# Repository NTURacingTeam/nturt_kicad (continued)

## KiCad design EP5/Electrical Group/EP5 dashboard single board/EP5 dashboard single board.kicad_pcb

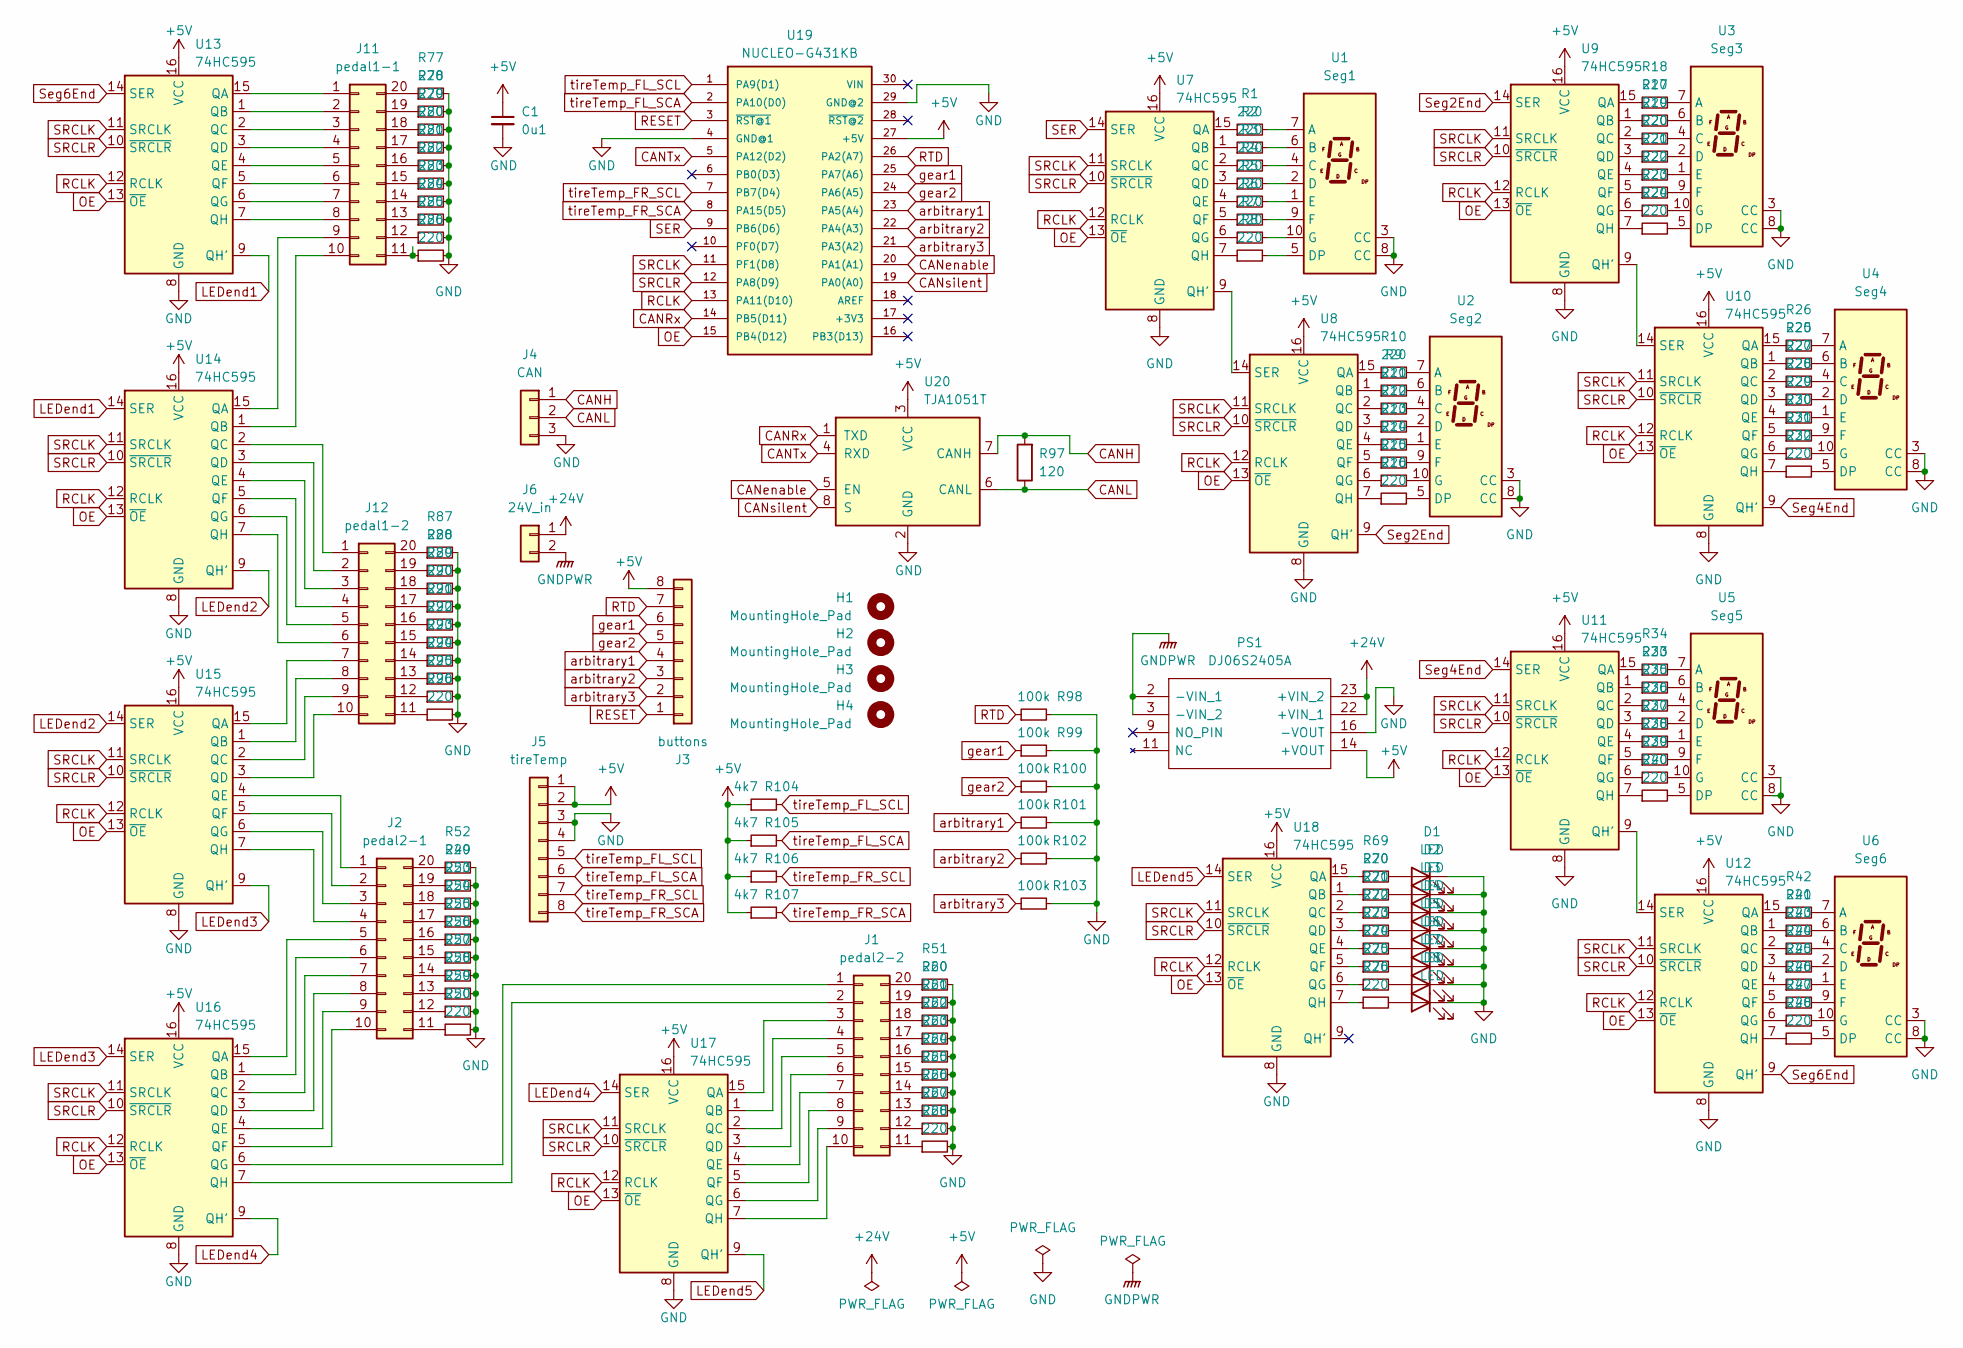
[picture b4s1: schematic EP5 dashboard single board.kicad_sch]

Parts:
C1: 0u1; C_0805_2012Metric_Pad1.18x1.45mm_HandSolder
D1, D2, D3, D4, D5, D6, D7, D8: LED; LED_PLCC_2835
H1, H2, H3, H4: MountingHole_Pad; MountingHole_2.2mm_M2_DIN965_Pad_TopBottom
J1: pedal2-2; DIP-20_W7.62mm
J2: pedal2-1; DIP-20_W7.62mm
J3: buttons; JST_XH_B8B-XH-A_1x08_P2.50mm_Vertical
J4: CAN; JST_XH_B3B-XH-A_1x03_P2.50mm_Vertical
J5: tireTemp; JST_XH_B8B-XH-A_1x08_P2.50mm_Vertical
J6: 24V_in; JST_XH_B2B-XH-A_1x02_P2.50mm_Vertical
J11: pedal1-1; DIP-20_W7.62mm
J12: pedal1-2; DIP-20_W7.62mm
PS1: DJ06S2405A; DJ06S4805A; Mouser Part Number 108-DJ06S4805A
R1, R2, R3, R4, R5, R6, R7, R8, R9, R10, R11, R12, R13, R14, R15, R16, R17, R18, R19, R20, R21, R22, R23, R24, R25, R26, R27, R28, R29, R30, R31, R32, R33, R34, R35, R36, R37, R38, R39, R40, R41, R42, R43, R44, R45, R46, R47, R48, R49, R50, R51, R52, R53, R54, R55, R56, R57, R58, R59, R60, R61, R62, R63, R64, R65, R66, R67, R68, R69, R70, R71, R72, R73, R74, R75, R76, R77, R78, R79, R80, R81, R82, R83, R84, R85, R86, R87, R88, R89, R90, R91, R92, R93, R94, R95, R96: 220; R_0603_1608Metric_Pad0.98x0.95mm_HandSolder
R97: 120; R_0805_2012Metric
R98, R99, R100, R101, R102, R103: 100k; R_0805_2012Metric
R104, R105, R106, R107: 4k7; R_0805_2012Metric
U1: Seg1; 7SegmentLED_LTS6760_LTS6780
U2: Seg2; 7SegmentLED_LTS6760_LTS6780
U3: Seg3; 7SegmentLED_LTS6760_LTS6780
U4: Seg4; 7SegmentLED_LTS6760_LTS6780
U5: Seg5; 7SegmentLED_LTS6760_LTS6780
U6: Seg6; 7SegmentLED_LTS6760_LTS6780
U7, U8, U9, U10, U11, U12, U13, U14, U15, U16, U17, U18: 74HC595; SOIC-16_3.9x9.9mm_P1.27mm
U19: NUCLEO-G431KB; MANUFACTURER_PART_NUMBER NUCLEO-F303K8
U20: TJA1051T; SOIC-8_3.9x4.9mm_P1.27mm

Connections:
+5V: C1.1, J3.8, J5.1, J5.2, PS1.14 (+VOUT), R104.1, R105.1, R106.1, R107.1, U7.16 (VCC), U8.16 (VCC), U9.16 (VCC), U10.16 (VCC), U11.16 (VCC), U12.16 (VCC), U13.16 (VCC), U14.16 (VCC), U15.16 (VCC), U16.16 (VCC), U17.16 (VCC), U18.16 (VCC), U19.27 (+5V), U20.3 (VCC)
+24V: J6.1, PS1.22 (+VIN_1), PS1.23 (+VIN_2)
CANH: J4.1, R97.2, U20.7 (CANH)
CANL: J4.2, R97.1, U20.6 (CANL)
CANRx: U19.14 (PB5(D11)), U20.1 (TXD)
CANTx: U19.5 (PA12(D2)), U20.4 (RXD)
CANenable: U19.20 (PA1(A1)), U20.5 (EN)
CANsilent: U19.19 (PA0(A0)), U20.8 (S)
GND: C1.2, D1.1 (K), D2.1 (K), D3.1 (K), D4.1 (K), D5.1 (K), D6.1 (K), D7.1 (K), D8.1 (K), J4.3, J5.3, J5.4, PS1.16 (-VOUT), R49.2, R50.2, R51.2, R52.2, R53.2, R54.2, R55.2, R56.2, R57.2, R58.2, R59.2, R60.2, R61.2, R62.2, R63.2, R64.2, R65.2, R66.2, R67.2, R68.2, R77.2, R78.2, R79.2, R80.2, R81.2, R82.2, R83.2, R84.2, R85.2, R86.2, R87.2, R88.2, R89.2, R90.2, R91.2, R92.2, R93.2, R94.2, R95.2, R96.2, R98.2, R99.2, R100.2, R101.2, R102.2, R103.2, U1.3 (CC), U1.8 (CC), U2.3 (CC), U2.8 (CC), U3.3 (CC), U3.8 (CC), U4.3 (CC), U4.8 (CC), U5.3 (CC), U5.8 (CC), U6.3 (CC), U6.8 (CC), U7.8 (GND), U8.8 (GND), U9.8 (GND), U10.8 (GND), U11.8 (GND), U12.8 (GND), U13.8 (GND), U14.8 (GND), U15.8 (GND), U16.8 (GND), U17.8 (GND), U18.8 (GND), U19.4 (GND@1), U19.29 (GND@2), U20.2 (GND)
GNDPWR: J6.2, PS1.2 (-VIN_1), PS1.3 (-VIN_2)
LEDend1: U13.9 (QH'), U14.14 (SER)
LEDend2: U14.9 (QH'), U15.14 (SER)
LEDend3: U15.9 (QH'), U16.14 (SER)
LEDend4: U16.9 (QH'), U17.14 (SER)
LEDend5: U17.9 (QH'), U18.14 (SER)
unnamed: D1.2 (A), R69.2
unnamed: D2.2 (A), R70.2
unnamed: D3.2 (A), R71.2
unnamed: D4.2 (A), R72.2
unnamed: D5.2 (A), R73.2
unnamed: D6.2 (A), R74.2
unnamed: D7.2 (A), R75.2
unnamed: D8.2 (A), R76.2
unnamed: J1.1, U16.6 (QG)
unnamed: J1.2, U16.7 (QH)
unnamed: J1.3, U17.15 (QA)
unnamed: J1.4, U17.1 (QB)
unnamed: J1.5, U17.2 (QC)
unnamed: J1.6, U17.3 (QD)
unnamed: J1.7, U17.4 (QE)
unnamed: J1.8, U17.5 (QF)
unnamed: J1.9, U17.6 (QG)
unnamed: J1.10, U17.7 (QH)
unnamed: J1.11, R68.1
unnamed: J1.12, R67.1
unnamed: J1.13, R66.1
unnamed: J1.14, R65.1
unnamed: J1.15, R64.1
unnamed: J1.16, R63.1
unnamed: J1.17, R62.1
unnamed: J1.18, R61.1
unnamed: J1.19, R60.1
unnamed: J1.20, R51.1
unnamed: J2.1, U15.4 (QE)
unnamed: J2.2, U15.5 (QF)
unnamed: J2.3, U15.6 (QG)
unnamed: J2.4, U15.7 (QH)
unnamed: J2.5, U16.15 (QA)
unnamed: J2.6, U16.1 (QB)
unnamed: J2.7, U16.2 (QC)
unnamed: J2.8, U16.3 (QD)
unnamed: J2.9, U16.4 (QE)
unnamed: J2.10, U16.5 (QF)
unnamed: J2.11, R50.1
unnamed: J2.12, R59.1
unnamed: J2.13, R58.1
unnamed: J2.14, R57.1
unnamed: J2.15, R56.1
unnamed: J2.16, R55.1
unnamed: J2.17, R54.1
unnamed: J2.18, R53.1
unnamed: J2.19, R49.1
unnamed: J2.20, R52.1
unnamed: J11.1, U13.15 (QA)
unnamed: J11.2, U13.1 (QB)
unnamed: J11.3, U13.2 (QC)
unnamed: J11.4, U13.3 (QD)
unnamed: J11.5, U13.4 (QE)
unnamed: J11.6, U13.5 (QF)
unnamed: J11.7, U13.6 (QG)
unnamed: J11.8, U13.7 (QH)
unnamed: J11.9, U14.15 (QA)
unnamed: J11.10, U14.1 (QB)
unnamed: J11.11, R86.1
unnamed: J11.12, R85.1
unnamed: J11.13, R84.1
unnamed: J11.14, R83.1
unnamed: J11.15, R82.1
unnamed: J11.16, R81.1
unnamed: J11.17, R80.1
unnamed: J11.18, R79.1
unnamed: J11.19, R78.1
unnamed: J11.20, R77.1
unnamed: J12.1, U14.2 (QC)
unnamed: J12.2, U14.3 (QD)
unnamed: J12.3, U14.4 (QE)
unnamed: J12.4, U14.5 (QF)
unnamed: J12.5, U14.6 (QG)
unnamed: J12.6, U14.7 (QH)
unnamed: J12.7, U15.15 (QA)
unnamed: J12.8, U15.1 (QB)
unnamed: J12.9, U15.2 (QC)
unnamed: J12.10, U15.3 (QD)
unnamed: J12.11, R96.1
unnamed: J12.12, R95.1
unnamed: J12.13, R94.1
unnamed: J12.14, R93.1
unnamed: J12.15, R92.1
unnamed: J12.16, R91.1
unnamed: J12.17, R90.1
unnamed: J12.18, R89.1
unnamed: J12.19, R88.1
unnamed: J12.20, R87.1
unnamed: R1.2, U1.7 (A)
unnamed: R2.2, U1.6 (B)
unnamed: R3.2, U1.4 (C)
unnamed: R4.2, U1.2 (D)
unnamed: R8.2, U1.5 (DP)
unnamed: R5.2, U1.1 (E)
unnamed: R6.2, U1.9 (F)
unnamed: R7.2, U1.10 (G)
unnamed: R10.2, U2.7 (A)
unnamed: R9.2, U2.6 (B)
unnamed: R11.2, U2.4 (C)
unnamed: R12.2, U2.2 (D)
unnamed: R16.2, U2.5 (DP)
unnamed: R13.2, U2.1 (E)
unnamed: R14.2, U2.9 (F)
unnamed: R15.2, U2.10 (G)
unnamed: R18.2, U3.7 (A)
unnamed: R17.2, U3.6 (B)
unnamed: R19.2, U3.4 (C)
unnamed: R20.2, U3.2 (D)
unnamed: R24.2, U3.5 (DP)
unnamed: R21.2, U3.1 (E)
unnamed: R22.2, U3.9 (F)
unnamed: R23.2, U3.10 (G)
unnamed: R26.2, U4.7 (A)
unnamed: R25.2, U4.6 (B)
unnamed: R27.2, U4.4 (C)
unnamed: R28.2, U4.2 (D)
unnamed: R32.2, U4.5 (DP)
unnamed: R29.2, U4.1 (E)
unnamed: R30.2, U4.9 (F)
unnamed: R31.2, U4.10 (G)
unnamed: R34.2, U5.7 (A)
unnamed: R33.2, U5.6 (B)
unnamed: R35.2, U5.4 (C)
unnamed: R36.2, U5.2 (D)
unnamed: R40.2, U5.5 (DP)
unnamed: R37.2, U5.1 (E)
unnamed: R38.2, U5.9 (F)
unnamed: R39.2, U5.10 (G)
unnamed: R42.2, U6.7 (A)
unnamed: R41.2, U6.6 (B)
unnamed: R43.2, U6.4 (C)
unnamed: R44.2, U6.2 (D)
unnamed: R48.2, U6.5 (DP)
unnamed: R45.2, U6.1 (E)
unnamed: R46.2, U6.9 (F)
unnamed: R47.2, U6.10 (G)
unnamed: R1.1, U7.15 (QA)
unnamed: R2.1, U7.1 (QB)
unnamed: R3.1, U7.2 (QC)
unnamed: R4.1, U7.3 (QD)
unnamed: R5.1, U7.4 (QE)
unnamed: R6.1, U7.5 (QF)
unnamed: R7.1, U7.6 (QG)
unnamed: U7.9 (QH'), U8.14 (SER)
unnamed: R8.1, U7.7 (QH)
unnamed: R10.1, U8.15 (QA)
unnamed: R9.1, U8.1 (QB)
unnamed: R11.1, U8.2 (QC)
unnamed: R12.1, U8.3 (QD)
unnamed: R13.1, U8.4 (QE)
unnamed: R14.1, U8.5 (QF)
unnamed: R15.1, U8.6 (QG)
unnamed: R16.1, U8.7 (QH)
unnamed: R18.1, U9.15 (QA)
unnamed: R17.1, U9.1 (QB)
unnamed: R19.1, U9.2 (QC)
unnamed: R20.1, U9.3 (QD)
unnamed: R21.1, U9.4 (QE)
unnamed: R22.1, U9.5 (QF)
unnamed: R23.1, U9.6 (QG)
unnamed: R24.1, U9.7 (QH)
unnamed: R26.1, U10.15 (QA)
unnamed: R25.1, U10.1 (QB)
unnamed: R27.1, U10.2 (QC)
unnamed: R28.1, U10.3 (QD)
unnamed: R29.1, U10.4 (QE)
unnamed: R30.1, U10.5 (QF)
unnamed: R31.1, U10.6 (QG)
unnamed: R32.1, U10.7 (QH)
unnamed: U9.9 (QH'), U10.14 (SER)
unnamed: R34.1, U11.15 (QA)
unnamed: R33.1, U11.1 (QB)
unnamed: R35.1, U11.2 (QC)
unnamed: R36.1, U11.3 (QD)
unnamed: R37.1, U11.4 (QE)
unnamed: R38.1, U11.5 (QF)
unnamed: R39.1, U11.6 (QG)
unnamed: U11.9 (QH'), U12.14 (SER)
unnamed: R40.1, U11.7 (QH)
unnamed: R42.1, U12.15 (QA)
unnamed: R41.1, U12.1 (QB)
unnamed: R43.1, U12.2 (QC)
unnamed: R44.1, U12.3 (QD)
unnamed: R45.1, U12.4 (QE)
unnamed: R46.1, U12.5 (QF)
unnamed: R47.1, U12.6 (QG)
unnamed: R48.1, U12.7 (QH)
unnamed: R69.1, U18.15 (QA)
unnamed: R70.1, U18.1 (QB)
unnamed: R71.1, U18.2 (QC)
unnamed: R72.1, U18.3 (QD)
unnamed: R73.1, U18.4 (QE)
unnamed: R74.1, U18.5 (QF)
unnamed: R75.1, U18.6 (QG)
unnamed: R76.1, U18.7 (QH)
OE: U7.13 (~OE), U8.13 (~OE), U9.13 (~OE), U10.13 (~OE), U11.13 (~OE), U12.13 (~OE), U13.13 (~OE), U14.13 (~OE), U15.13 (~OE), U16.13 (~OE), U17.13 (~OE), U18.13 (~OE), U19.15 (PB4(D12))
RCLK: U7.12 (RCLK), U8.12 (RCLK), U9.12 (RCLK), U10.12 (RCLK), U11.12 (RCLK), U12.12 (RCLK), U13.12 (RCLK), U14.12 (RCLK), U15.12 (RCLK), U16.12 (RCLK), U17.12 (RCLK), U18.12 (RCLK), U19.13 (PA11(D10))
RESET: J3.1, U19.3 (~RST@1)
RTD: J3.7, R98.1, U19.26 (PA2(A7))
SER: U7.14 (SER), U19.9 (PB6(D6))
SRCLK: U7.11 (SRCLK), U8.11 (SRCLK), U9.11 (SRCLK), U10.11 (SRCLK), U11.11 (SRCLK), U12.11 (SRCLK), U13.11 (SRCLK), U14.11 (SRCLK), U15.11 (SRCLK), U16.11 (SRCLK), U17.11 (SRCLK), U18.11 (SRCLK), U19.11 (PF1(D8))
SRCLR: U7.10 (~SRCLR), U8.10 (~SRCLR), U9.10 (~SRCLR), U10.10 (~SRCLR), U11.10 (~SRCLR), U12.10 (~SRCLR), U13.10 (~SRCLR), U14.10 (~SRCLR), U15.10 (~SRCLR), U16.10 (~SRCLR), U17.10 (~SRCLR), U18.10 (~SRCLR), U19.12 (PA8(D9))
Seg2End: U8.9 (QH'), U9.14 (SER)
Seg4End: U10.9 (QH'), U11.14 (SER)
Seg6End: U12.9 (QH'), U13.14 (SER)
arbitrary1: J3.4, R101.1, U19.23 (PA5(A4))
arbitrary2: J3.3, R102.1, U19.22 (PA4(A3))
arbitrary3: J3.2, R103.1, U19.21 (PA3(A2))
gear1: J3.6, R99.1, U19.25 (PA7(A6))
gear2: J3.5, R100.1, U19.24 (PA6(A5))
tireTemp_FL_SCA: J5.6, R105.2, U19.2 (PA10(D0))
tireTemp_FL_SCL: J5.5, R104.2, U19.1 (PA9(D1))
tireTemp_FR_SCA: J5.8, R107.2, U19.8 (PA15(D5))
tireTemp_FR_SCL: J5.7, R106.2, U19.7 (PB7(D4))

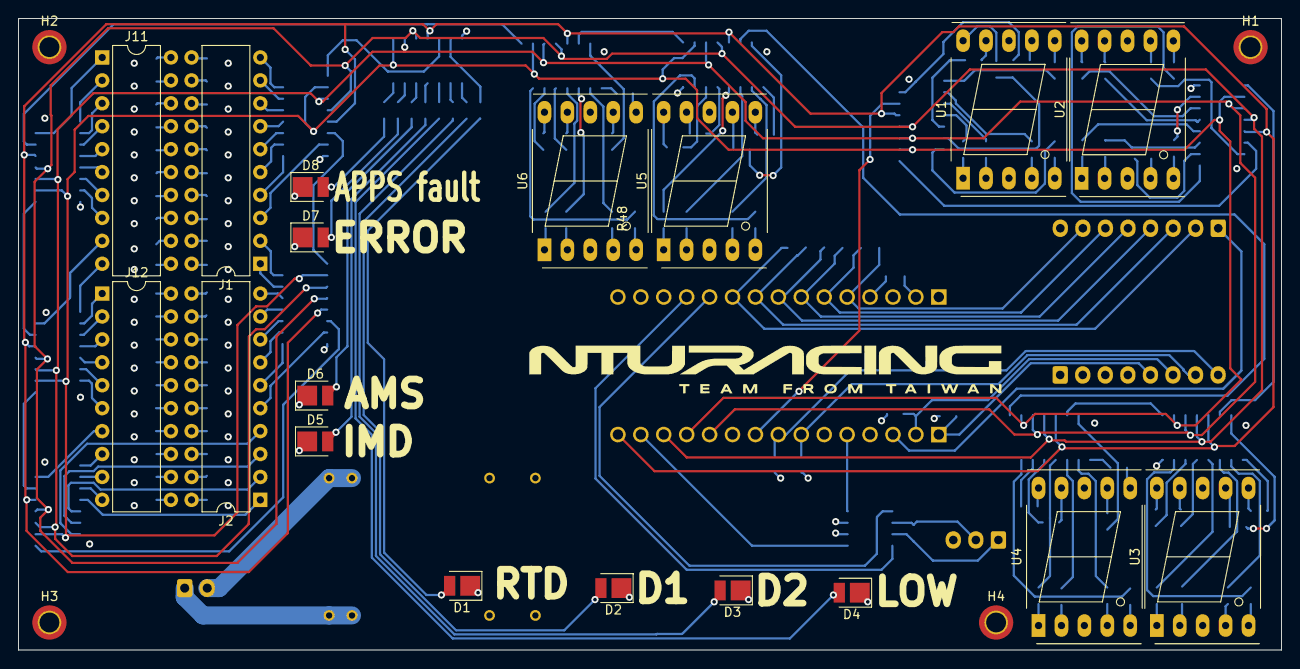
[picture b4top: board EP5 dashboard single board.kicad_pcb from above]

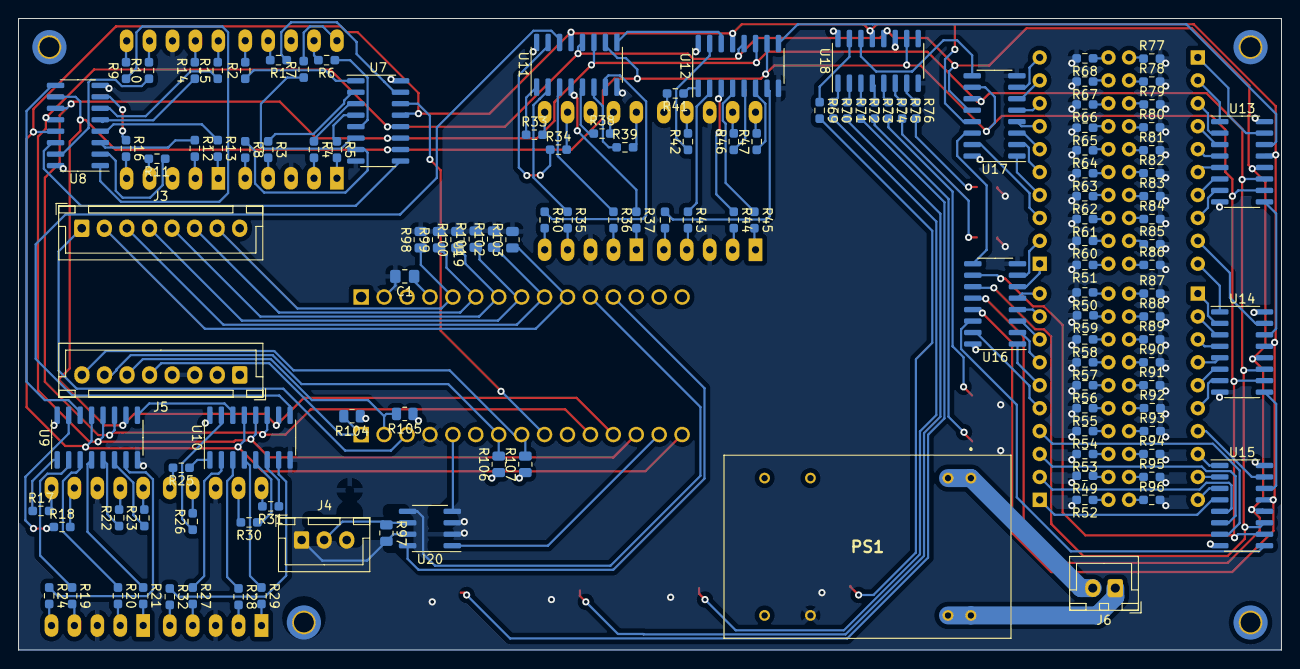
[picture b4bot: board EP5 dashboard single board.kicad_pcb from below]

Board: 4 copper layers, 140.0 x 70.0 mm, 149 parts (127 on the bottom side), 229 nets.

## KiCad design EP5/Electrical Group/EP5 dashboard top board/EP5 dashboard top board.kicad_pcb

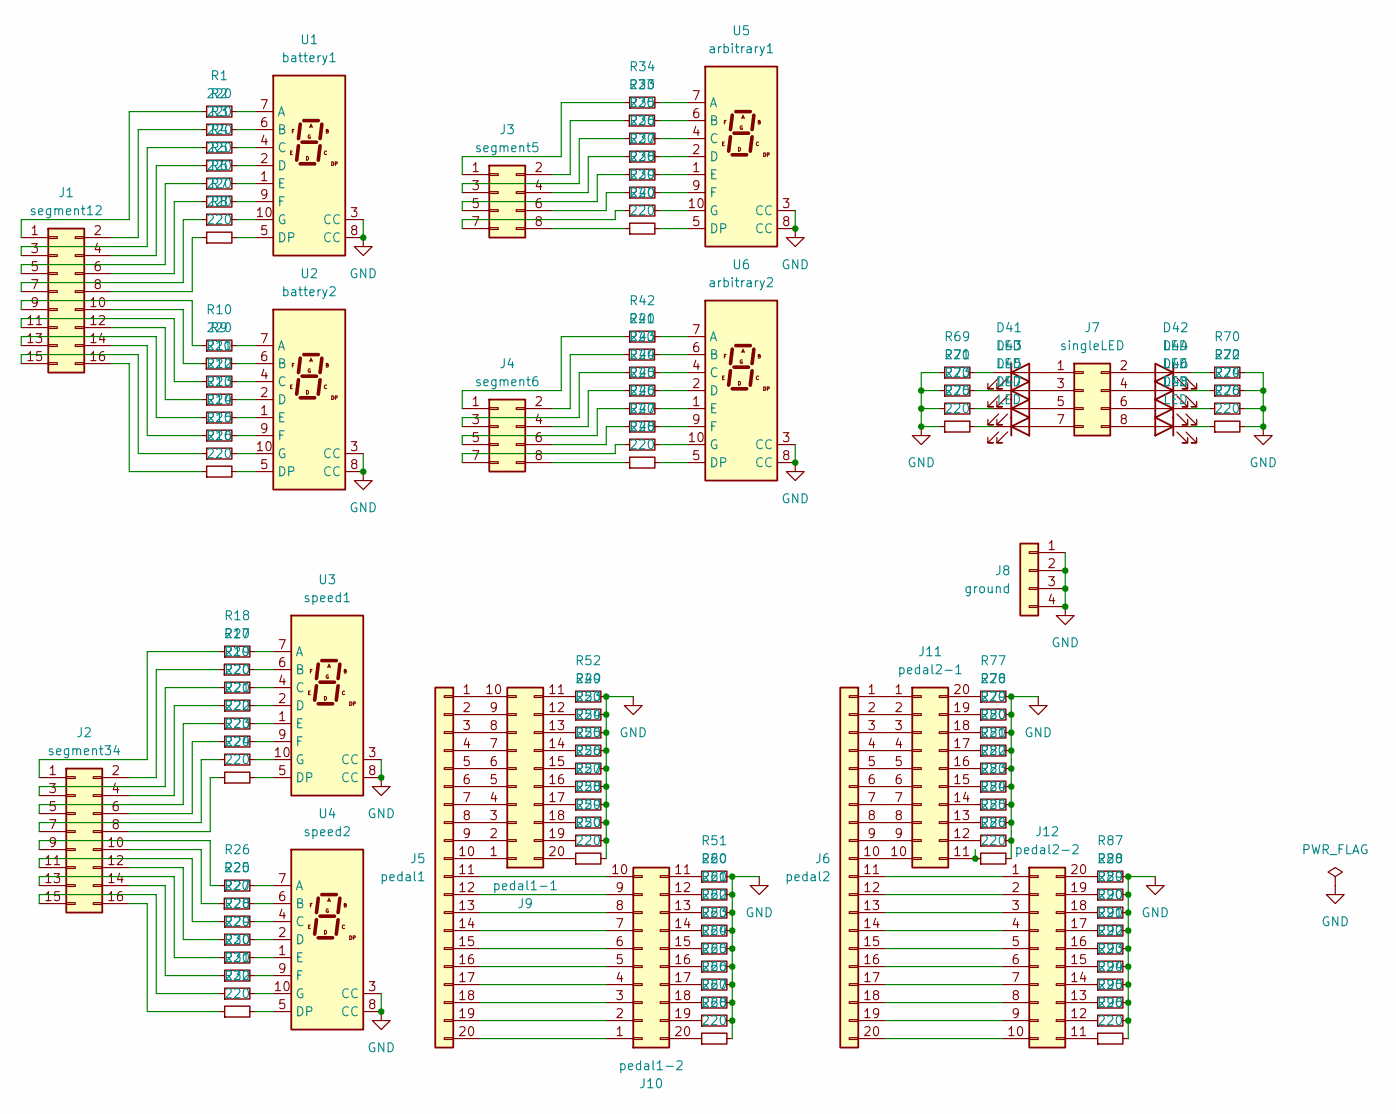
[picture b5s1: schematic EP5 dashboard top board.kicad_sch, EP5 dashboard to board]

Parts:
D41, D42, D43, D44, D45, D46, D47, D48: LED; LED_PLCC_2835
J1: segment12; PinHeader_2x08_P2.54mm_Vertical
J2: segment34; PinHeader_2x08_P2.54mm_Vertical
J3: segment5; PinHeader_2x04_P2.54mm_Vertical
J4: segment6; PinHeader_2x04_P2.54mm_Vertical
J5: pedal1; PinHeader_1x20_P2.54mm_Vertical
J6: pedal2; PinHeader_1x20_P2.54mm_Vertical
J7: singleLED; PinHeader_2x04_P2.54mm_Vertical
J8: ground; PinHeader_1x04_P2.54mm_Vertical
J9: pedal1-1; DIP-20_W7.62mm
J10: pedal1-2; DIP-20_W7.62mm
J11: pedal2-1; DIP-20_W7.62mm
J12: pedal2-2; DIP-20_W7.62mm
R1, R2, R3, R4, R5, R6, R7, R8, R9, R10, R11, R12, R13, R14, R15, R16, R17, R18, R19, R20, R21, R22, R23, R24, R25, R26, R27, R28, R29, R30, R31, R32, R33, R34, R35, R36, R37, R38, R39, R40, R41, R42, R43, R44, R45, R46, R47, R48, R69, R70, R71, R72, R73, R74, R75, R76: 220; R_0805_2012Metric
R49, R50, R51, R52, R53, R54, R55, R56, R57, R58, R59, R60, R61, R62, R63, R64, R65, R66, R67, R68, R77, R78, R79, R80, R81, R82, R83, R84, R85, R86, R87, R88, R89, R90, R91, R92, R93, R94, R95, R96: 220; R_0603_1608Metric_Pad0.98x0.95mm_HandSolder
U1: battery1; 7SegmentLED_LTS6760_LTS6780
U2: battery2; 7SegmentLED_LTS6760_LTS6780
U3: speed1; 7SegmentLED_LTS6760_LTS6780
U4: speed2; 7SegmentLED_LTS6760_LTS6780
U5: arbitrary1; 7SegmentLED_LTS6760_LTS6780
U6: arbitrary2; 7SegmentLED_LTS6760_LTS6780

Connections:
GND: J8.1, J8.2, J8.3, J8.4, R49.2, R50.2, R51.2, R52.2, R53.2, R54.2, R55.2, R56.2, R57.2, R58.2, R59.2, R60.2, R61.2, R62.2, R63.2, R64.2, R65.2, R66.2, R67.2, R68.2, R69.1, R70.2, R71.1, R72.2, R73.1, R74.2, R75.1, R76.2, R77.2, R78.2, R79.2, R80.2, R81.2, R82.2, R83.2, R84.2, R85.2, R86.2, R87.2, R88.2, R89.2, R90.2, R91.2, R92.2, R93.2, R94.2, R95.2, R96.2, U1.3 (CC), U1.8 (CC), U2.3 (CC), U2.8 (CC), U3.3 (CC), U3.8 (CC), U4.3 (CC), U4.8 (CC), U5.3 (CC), U5.8 (CC), U6.3 (CC), U6.8 (CC)
unnamed: D41.2 (A), J7.1
unnamed: D41.1 (K), R69.2
unnamed: D42.2 (A), J7.2
unnamed: D42.1 (K), R70.1
unnamed: D43.2 (A), J7.3
unnamed: D43.1 (K), R71.2
unnamed: D44.2 (A), J7.4
unnamed: D44.1 (K), R72.1
unnamed: D45.2 (A), J7.5
unnamed: D45.1 (K), R73.2
unnamed: D46.2 (A), J7.6
unnamed: D46.1 (K), R74.1
unnamed: D47.2 (A), J7.7
unnamed: D47.1 (K), R75.2
unnamed: D48.2 (A), J7.8
unnamed: D48.1 (K), R76.1
unnamed: J1.1, R1.1
unnamed: J1.2, R2.1
unnamed: J1.3, R3.1
unnamed: J1.4, R4.1
unnamed: J1.5, R5.1
unnamed: J1.6, R6.1
unnamed: J1.7, R7.1
unnamed: J1.8, R8.1
unnamed: J1.9, R10.1
unnamed: J1.10, R9.1
unnamed: J1.11, R11.1
unnamed: J1.12, R12.1
unnamed: J1.13, R13.1
unnamed: J1.14, R14.1
unnamed: J1.15, R15.1
unnamed: J1.16, R16.1
unnamed: J2.1, R18.1
unnamed: J2.2, R17.1
unnamed: J2.3, R19.1
unnamed: J2.4, R20.1
unnamed: J2.5, R21.1
unnamed: J2.6, R22.1
unnamed: J2.7, R23.1
unnamed: J2.8, R24.1
unnamed: J2.9, R26.1
unnamed: J2.10, R25.1
unnamed: J2.11, R27.1
unnamed: J2.12, R28.1
unnamed: J2.13, R29.1
unnamed: J2.14, R30.1
unnamed: J2.15, R31.1
unnamed: J2.16, R32.1
unnamed: J3.1, R34.1
unnamed: J3.2, R33.1
unnamed: J3.3, R35.1
unnamed: J3.4, R36.1
unnamed: J3.5, R37.1
unnamed: J3.6, R38.1
unnamed: J3.7, R39.1
unnamed: J3.8, R40.1
unnamed: J4.1, R42.1
unnamed: J4.2, R41.1
unnamed: J4.3, R43.1
unnamed: J4.4, R44.1
unnamed: J4.5, R45.1
unnamed: J4.6, R46.1
unnamed: J4.7, R47.1
unnamed: J4.8, R48.1
unnamed: J5.1, J9.10
unnamed: J5.2, J9.9
unnamed: J5.3, J9.8
unnamed: J5.4, J9.7
unnamed: J5.5, J9.6
unnamed: J5.6, J9.5
unnamed: J5.7, J9.4
unnamed: J5.8, J9.3
unnamed: J5.9, J9.2
unnamed: J5.10, J9.1
unnamed: J9.11, R52.1
unnamed: J9.12, R49.1
unnamed: J9.13, R53.1
unnamed: J9.14, R54.1
unnamed: J9.15, R55.1
unnamed: J9.16, R56.1
unnamed: J9.17, R57.1
unnamed: J9.18, R58.1
unnamed: J9.19, R59.1
unnamed: J9.20, R50.1
unnamed: J5.20, J10.1
unnamed: J5.19, J10.2
unnamed: J5.18, J10.3
unnamed: J5.17, J10.4
unnamed: J5.16, J10.5
unnamed: J5.15, J10.6
unnamed: J5.14, J10.7
unnamed: J5.13, J10.8
unnamed: J5.12, J10.9
unnamed: J5.11, J10.10
unnamed: J10.11, R51.1
unnamed: J10.12, R60.1
unnamed: J10.13, R61.1
unnamed: J10.14, R62.1
unnamed: J10.15, R63.1
unnamed: J10.16, R64.1
unnamed: J10.17, R65.1
unnamed: J10.18, R66.1
unnamed: J10.19, R67.1
unnamed: J10.20, R68.1
unnamed: J6.1, J11.1
unnamed: J6.2, J11.2
unnamed: J6.3, J11.3
unnamed: J6.4, J11.4
unnamed: J6.5, J11.5
unnamed: J6.6, J11.6
unnamed: J6.7, J11.7
unnamed: J6.8, J11.8
unnamed: J6.9, J11.9
unnamed: J6.10, J11.10
unnamed: J11.11, R86.1
unnamed: J11.12, R85.1
unnamed: J11.13, R84.1
unnamed: J11.14, R83.1
unnamed: J11.15, R82.1
unnamed: J11.16, R81.1
unnamed: J11.17, R80.1
unnamed: J11.18, R79.1
unnamed: J11.19, R78.1
unnamed: J11.20, R77.1
unnamed: J6.11, J12.1
unnamed: J6.12, J12.2
unnamed: J6.13, J12.3
unnamed: J6.14, J12.4
unnamed: J6.15, J12.5
unnamed: J6.16, J12.6
unnamed: J6.17, J12.7
unnamed: J6.18, J12.8
unnamed: J6.19, J12.9
unnamed: J6.20, J12.10
unnamed: J12.11, R96.1
unnamed: J12.12, R95.1
unnamed: J12.13, R94.1
unnamed: J12.14, R93.1
unnamed: J12.15, R92.1
unnamed: J12.16, R91.1
unnamed: J12.17, R90.1
unnamed: J12.18, R89.1
unnamed: J12.19, R88.1
unnamed: J12.20, R87.1
unnamed: R1.2, U1.7 (A)
unnamed: R2.2, U1.6 (B)
unnamed: R3.2, U1.4 (C)
unnamed: R4.2, U1.2 (D)
unnamed: R8.2, U1.5 (DP)
unnamed: R5.2, U1.1 (E)
unnamed: R6.2, U1.9 (F)
unnamed: R7.2, U1.10 (G)
unnamed: R10.2, U2.7 (A)
unnamed: R9.2, U2.6 (B)
unnamed: R11.2, U2.4 (C)
unnamed: R12.2, U2.2 (D)
unnamed: R16.2, U2.5 (DP)
unnamed: R13.2, U2.1 (E)
unnamed: R14.2, U2.9 (F)
unnamed: R15.2, U2.10 (G)
unnamed: R18.2, U3.7 (A)
unnamed: R17.2, U3.6 (B)
unnamed: R19.2, U3.4 (C)
unnamed: R20.2, U3.2 (D)
unnamed: R24.2, U3.5 (DP)
unnamed: R21.2, U3.1 (E)
unnamed: R22.2, U3.9 (F)
unnamed: R23.2, U3.10 (G)
unnamed: R26.2, U4.7 (A)
unnamed: R25.2, U4.6 (B)
unnamed: R27.2, U4.4 (C)
unnamed: R28.2, U4.2 (D)
unnamed: R32.2, U4.5 (DP)
unnamed: R29.2, U4.1 (E)
unnamed: R30.2, U4.9 (F)
unnamed: R31.2, U4.10 (G)
unnamed: R34.2, U5.7 (A)
unnamed: R33.2, U5.6 (B)
unnamed: R35.2, U5.4 (C)
unnamed: R36.2, U5.2 (D)
unnamed: R40.2, U5.5 (DP)
unnamed: R37.2, U5.1 (E)
unnamed: R38.2, U5.9 (F)
unnamed: R39.2, U5.10 (G)
unnamed: R42.2, U6.7 (A)
unnamed: R41.2, U6.6 (B)
unnamed: R43.2, U6.4 (C)
unnamed: R44.2, U6.2 (D)
unnamed: R48.2, U6.5 (DP)
unnamed: R45.2, U6.1 (E)
unnamed: R46.2, U6.9 (F)
unnamed: R47.2, U6.10 (G)

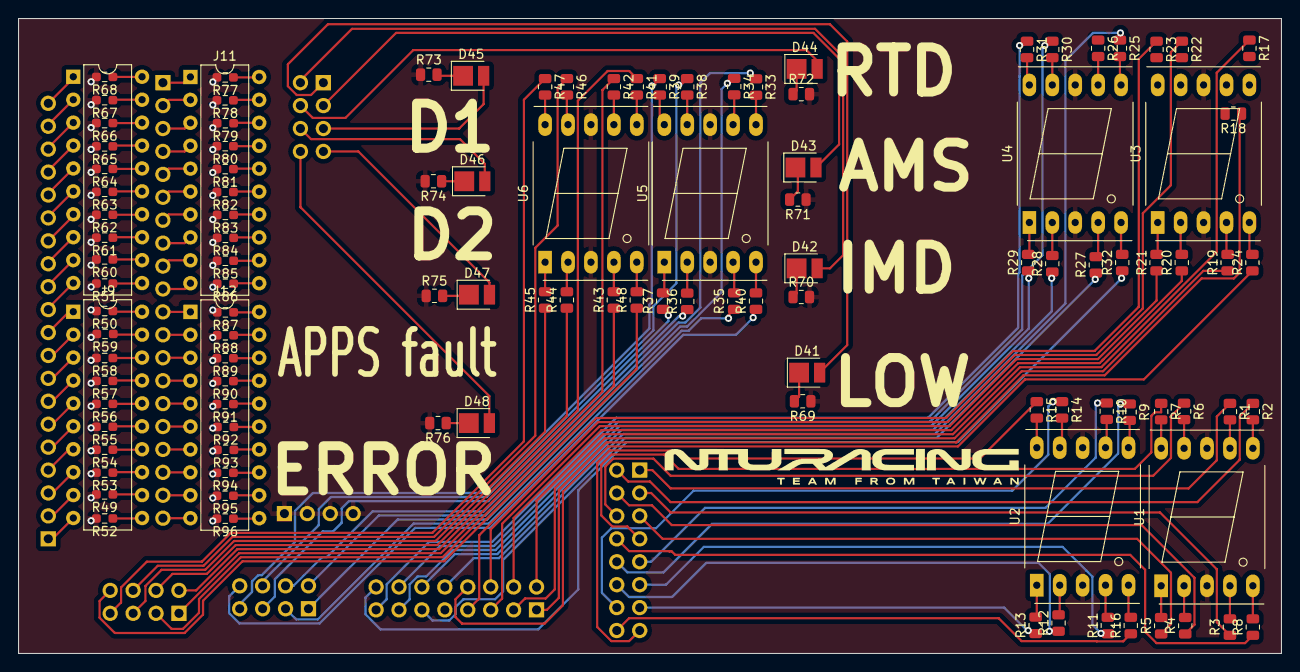
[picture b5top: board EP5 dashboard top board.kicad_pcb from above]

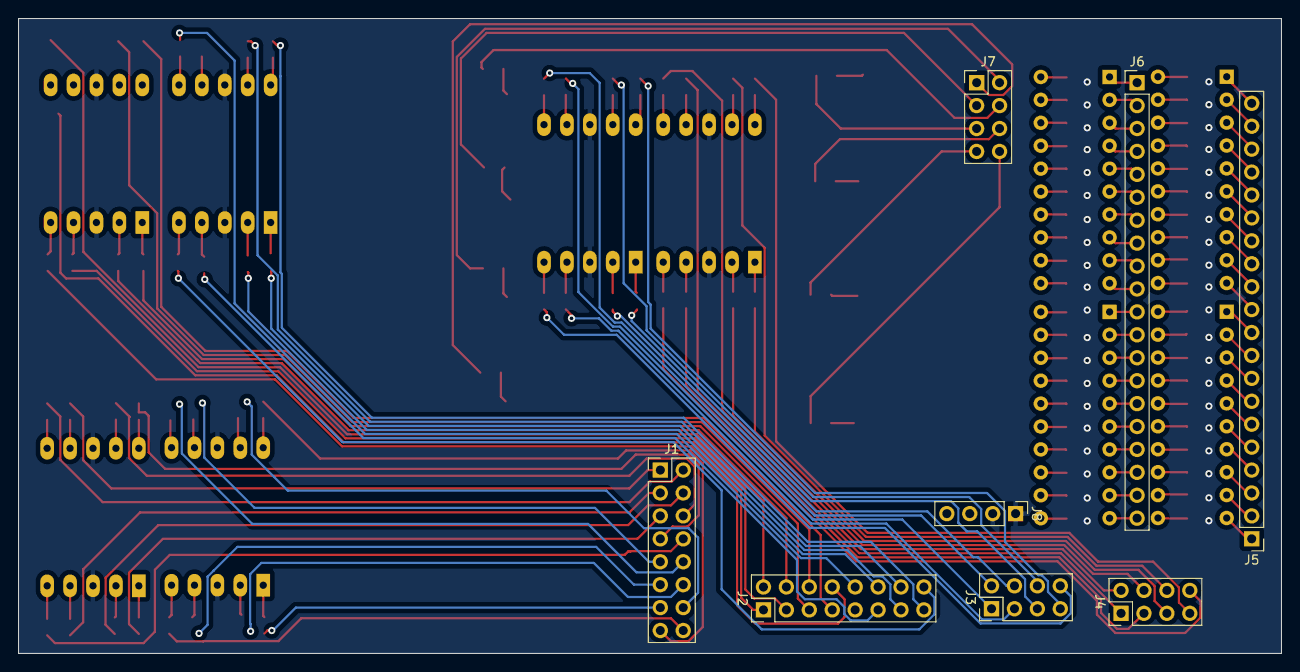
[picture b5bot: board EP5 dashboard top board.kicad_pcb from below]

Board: 2 copper layers, 140.0 x 70.4 mm, 122 parts (8 on the bottom side), 193 nets.

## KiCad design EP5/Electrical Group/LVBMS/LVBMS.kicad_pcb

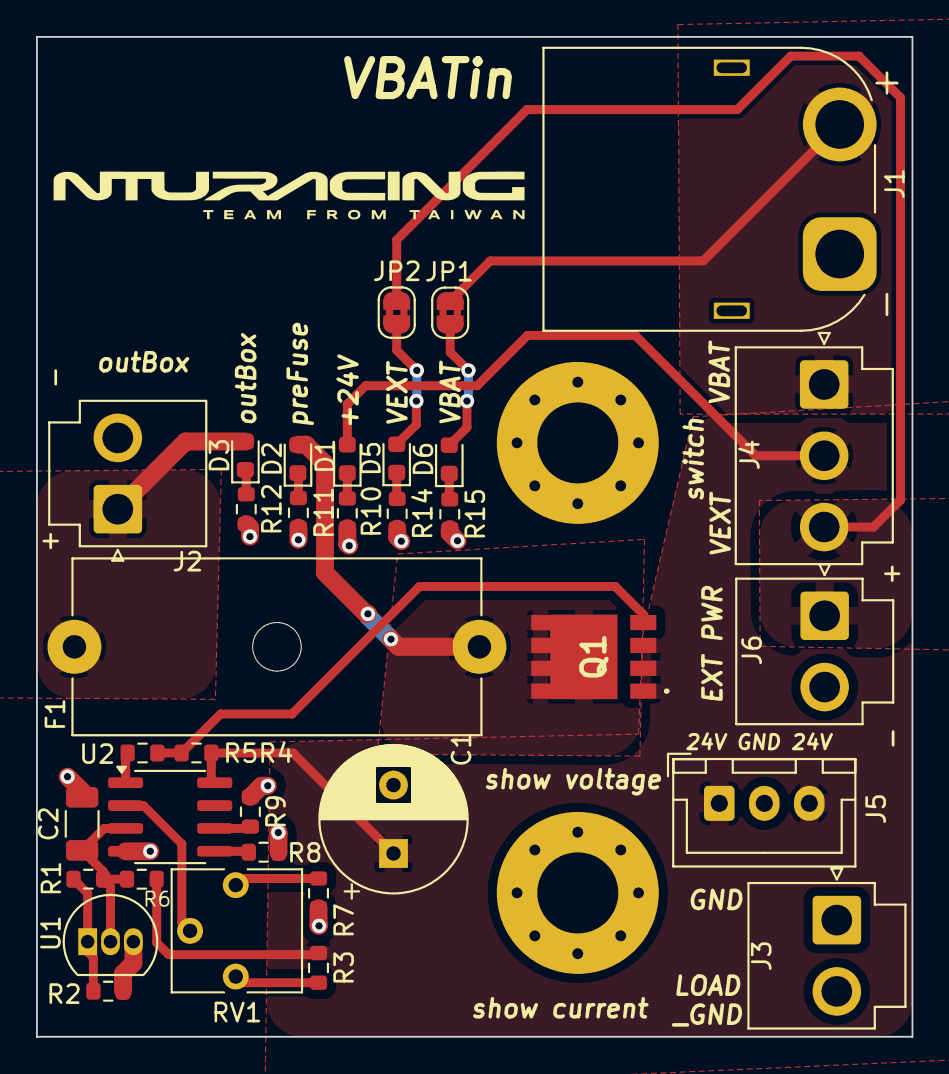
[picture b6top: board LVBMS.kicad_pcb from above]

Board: 2 copper layers, 48.6 x 55.5 mm, 36 parts (0 on the bottom side), 23 nets.

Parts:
C1: 220u; CP_Radial_D8.0mm_P3.80mm
C2: 10u 35V; C_1206_3216Metric
D1: BLUE 24VGood; LED_0603_1608Metric
D2: RED 24Vprefuse; LED_0603_1608Metric
D3: RED 24Voutbox; LED_0603_1608Metric
D5: WHITE 24Vext; LED_0603_1608Metric
D6: GREEN 24Vbat; LED_0603_1608Metric
F1: Fuse; Fuseholder_Cylinder-5x20mm_Schurter_0031_8201_Horizontal_Op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
H1, H2: MountingHole_Pad; MountingHole_4.5mm_Pad_Via
J1: BAT; AMASS_XT60PW-M_1x02_P7.20mm_Horizontal
J2: OUT; JST_VH_B2P-VH-B_1x02_P3.96mm_Vertical
J3: showCurrent; JST_VH_B2P-VH-B_1x02_P3.96mm_Vertical
J4: switch; JST_VH_B3P-VH_1x03_P3.96mm_Vertical
J5: showVoltage; JST_XH_B3B-XH-A_1x03_P2.50mm_Vertical
J6: extPWR; JST_VH_B2P-VH-B_1x02_P3.96mm_Vertical
JP1: VBAT; SolderJumper-2_P1.3mm_Bridged2Bar_RoundedPad1.0x1.5mm
JP2: VEXT; SolderJumper-2_P1.3mm_Bridged2Bar_RoundedPad1.0x1.5mm
Q1: TPCA8120,L1Q; TPH4R003NLL1Q
R1: 12k; R_0603_1608Metric
R2: 82k; R_0603_1608Metric
R3, R7: 390k; R_0603_1608Metric
R4, R5: 100k; R_0603_1608Metric
R6, R8, R10, R11, R12, R14, R15: 10k; R_0603_1608Metric
R9: 10M; R_0603_1608Metric
RV1: 100k; Potentiometer_Vishay_T73YP_Vertical
U1: LM4041LP-ADJ; TO-92_Inline
U2: LM2903; SOIC-8_3.9x4.9mm_P1.27mm

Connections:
+24V: C1.1, D1.2 (A), J4.2, J5.1, J5.3, Q1.1 (S_1), Q1.2 (S_2), Q1.3 (S_3), R3.1, R4.1, R6.1, U2.8 (V+)
/+24V_outbox: D3.2 (A), F1.2, J2.1
/+24V_prefuse: D2.2 (A), F1.1, Q1.5 (D_1), Q1.6 (D_2), Q1.7 (D_3), Q1.8 (D_4), Q1.9 (D_5)
/VBAT: J1.2, J4.1, JP1.2 (B)
/VEXT: J4.3, J6.1, JP2.2 (B)
GND: J1.1, J3.1, J5.2, J6.2
GNDPWR: C1.2, C2.2, H1.1, H2.1, J2.2, J3.2, R2.2, R7.2, R8.1, R9.1, R10.2, R11.2, R12.2, R14.2, R15.2, U1.3 (A), U2.4 (V-)
unnamed: D1.1 (K), R10.1
unnamed: D2.1 (K), R11.1
unnamed: D3.1 (K), R12.1
unnamed: D5.2 (A), JP2.1 (A)
unnamed: D5.1 (K), R14.1
unnamed: D6.2 (A), JP1.1 (A)
unnamed: D6.1 (K), R15.1
unnamed: Q1.4 (G), R4.2, R5.2
unnamed: R3.2, RV1.3
unnamed: R5.1, U2.1
unnamed: R7.1, RV1.1
unnamed: R1.2, R2.1, U1.1 (FB)
unnamed: C2.1, R1.1, R6.2, U1.2 (K), U2.3 (+)
unnamed: RV1.2, U2.2 (-)
unnamed: R8.2, U2.5 (+)
unnamed: R9.2, U2.6 (-)
